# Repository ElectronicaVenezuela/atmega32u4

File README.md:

# atmega32u4
implementacion atmega usb y lector sd

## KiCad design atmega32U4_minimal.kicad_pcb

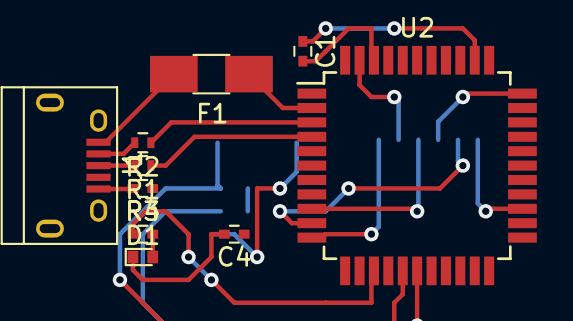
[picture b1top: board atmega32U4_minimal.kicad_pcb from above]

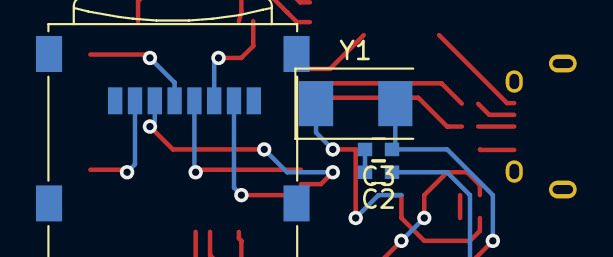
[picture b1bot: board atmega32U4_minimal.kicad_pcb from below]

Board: 2 copper layers, 14 parts (4 on the bottom side), 17 nets.

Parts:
C1: 0.1UF-0402-16V-10%; C_0402
C2, C3: 18PF-0603-50V-5%; C_0603
C4: 1.0UF-0402-16V-10%; C_0402
D1: LED; LED_0402
F1: Fuse; Fuse_SMD1206_HandSoldering
J1: USB_B_Micro; USB_Micro-B
J2: Micro_SD_Card; microSD_Card_Receptacle_Wuerth_693072010801
R1, R2: 22; R_0402
R3: 1K0402; C_0402
R4: 10k0402; C_0402
U2: ATmega32U4-AU; LQFP-44_10x10mm_Pitch0.8mm
Y1: Crystal; Crystal_SMD_0603-2pin_6.0x3.5mm

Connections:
GND: C1.1, C2.2, C3.2, C4.2, D1.1, J1.5, J2.6, R4.2, U2.5, U2.13, U2.15, U2.23, U2.35, U2.43
unnamed: C1.2, U2.42
unnamed: C2.1, U2.17, Y1.1
unnamed: C3.1, U2.16, Y1.2
unnamed: C4.1, U2.6
unnamed: D1.2, R3.2
unnamed: F1.2, J1.1
unnamed: J1.2, R2.2
unnamed: J1.3, R1.2
unnamed: J2.2, U2.25
unnamed: J2.3, U2.10
unnamed: J2.4, U2.33
unnamed: J2.5, U2.9
unnamed: J2.7, U2.11
unnamed: R1.1, U2.4
unnamed: R2.1, U2.3
VBUS: F1.1, R3.1, R4.1, U2.2, U2.7, U2.14, U2.24, U2.34, U2.44
